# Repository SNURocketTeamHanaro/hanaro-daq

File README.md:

# Hanaro DAQ
A simple, low-cost, crude data acquisition system for combustion test of solid rocket motor.

### Specification
Hanaro DAQ for 200kgf horizontal combustion test system is a super low-cost data acquisition system. Equipped with two transducer for pressure sensor on the left and right side of the chamber top, and an instrumental amplifier for a single 200kgf load cell. Data is retrieved and recorded every 6-7 ms.

### Contents
- Hanaro DAQ PCB board designed with KiCAD v5.0.0
- Simple Arduino code for acquisition of data
- Data acquired with the system

### Credit
[Jaerin Lee](https://github.com/ironjr)  
Lead Electronics and Software Developer  
SNU Rocket Team Hanaro

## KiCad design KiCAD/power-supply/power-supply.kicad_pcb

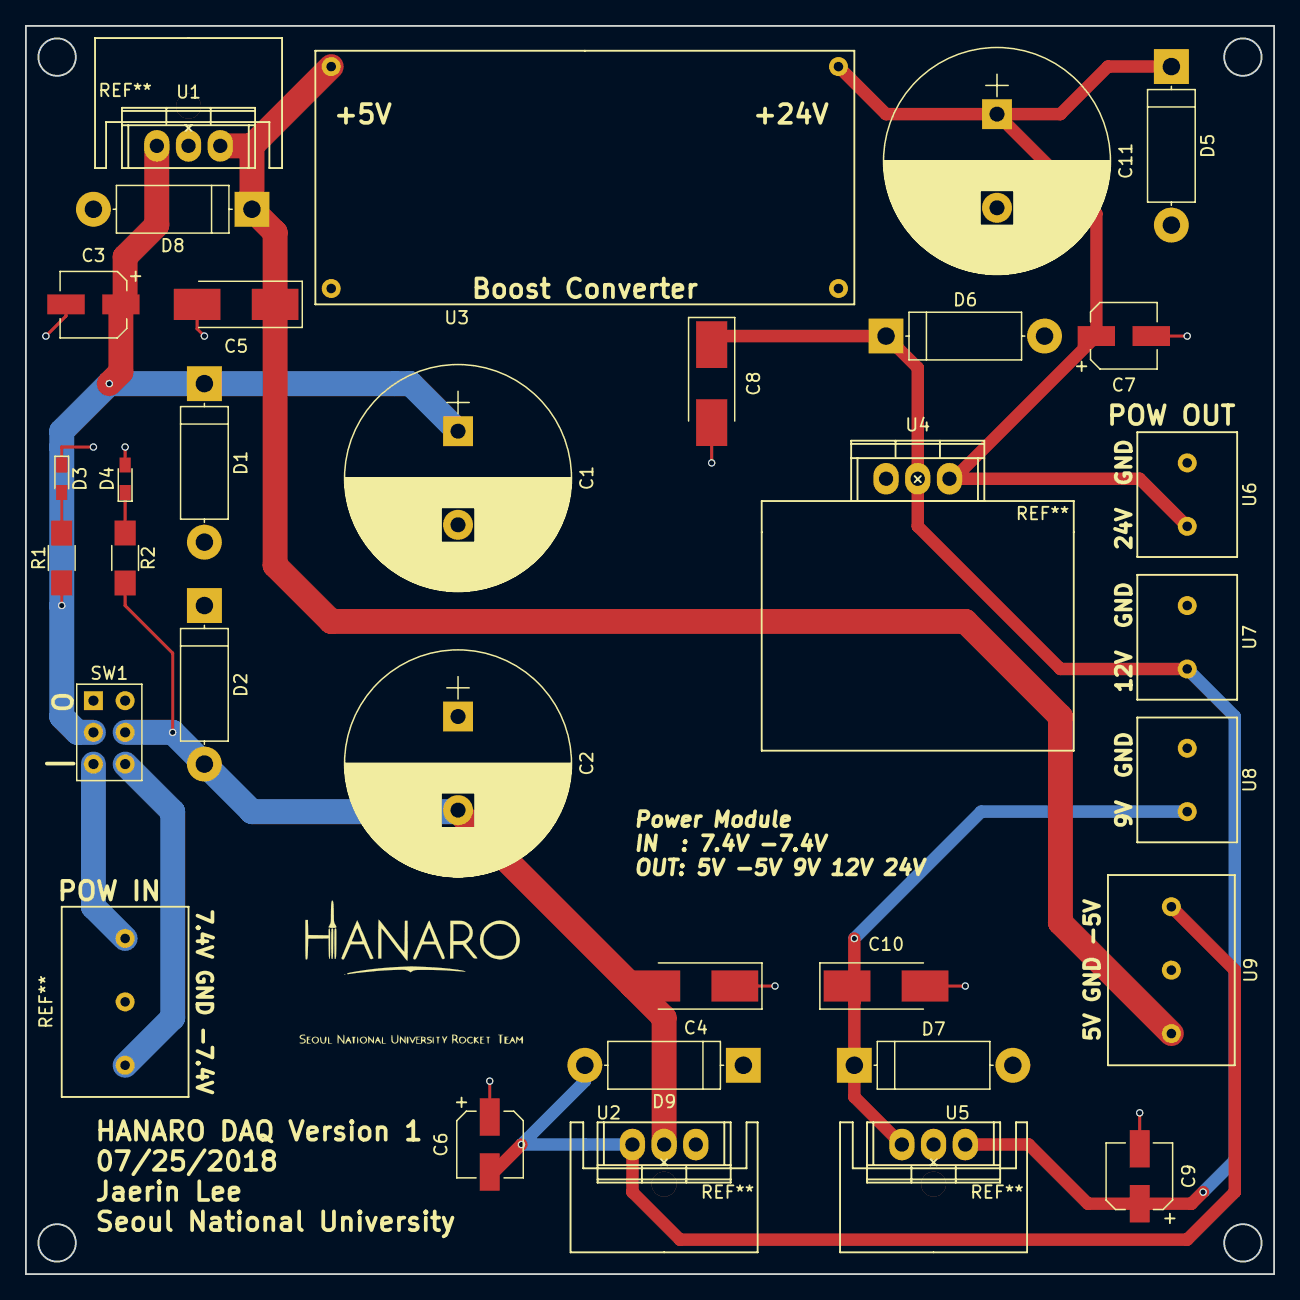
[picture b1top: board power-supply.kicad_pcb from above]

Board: 2 copper layers, 100.0 x 100.0 mm, 32 parts (0 on the bottom side), 10 nets.

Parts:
C1, C2, C11: CP1; CP_Radial_D18.0mm_P7.50mm
C3, C6, C7, C9: CP1; CP_Elec_5x5.3
C4, C5, C8, C10: CP1; CP_Tantalum_Case-C_EIA-6032-28_Hand
D1, D2, D5, D6, D7, D8, D9: D; D_5W_P12.70mm_Horizontal
D3, D4: LED; LED_0603_HandSoldering
R1, R2: R; R_1206_HandSoldering
SW1: SW_DPDT_x2; SW_NKK_G1xJP
U1: L7805; TO-220
U2: L7905; TO-220
U3: BoostConv; Boost.Conv
U4: LM1085-12; TO-220
U5: L7809; TO-220
U6, U7, U8: Conn2; Connector.2pin
U9: Conn3; Connector.3pin

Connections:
/V5out: C5.1, D8.1, U1.3, U3.1, U9.1
/V9out: C10.1, D7.1, U5.3, U8.1
/V12out: C8.1, C9.1, D6.1, U4.2, U5.1, U7.1
/V24out: C7.1, C11.1, D5.1, U3.3, U4.3, U6.1
/V-5out: C6.2, D9.2, U2.3, U9.3
GND: C1.2, C2.1, C3.2, C4.1, C5.2, C6.1, C7.2, C8.2, C9.2, C10.2, C11.2, D1.2, D2.1, D3.1, D4.2, D5.2, D6.2, D7.2, D8.2, D9.1, U1.2, U2.1, U3.2, U3.4, U4.1, U5.2, U6.2, U7.2, U8.2, U9.2
unnamed: C1.1, C3.1, D1.1, R1.1, SW1.2, U1.1
unnamed: C2.2, C4.2, D2.2, R2.2, SW1.5, U2.2
unnamed: D3.2, R1.2
unnamed: D4.1, R2.1

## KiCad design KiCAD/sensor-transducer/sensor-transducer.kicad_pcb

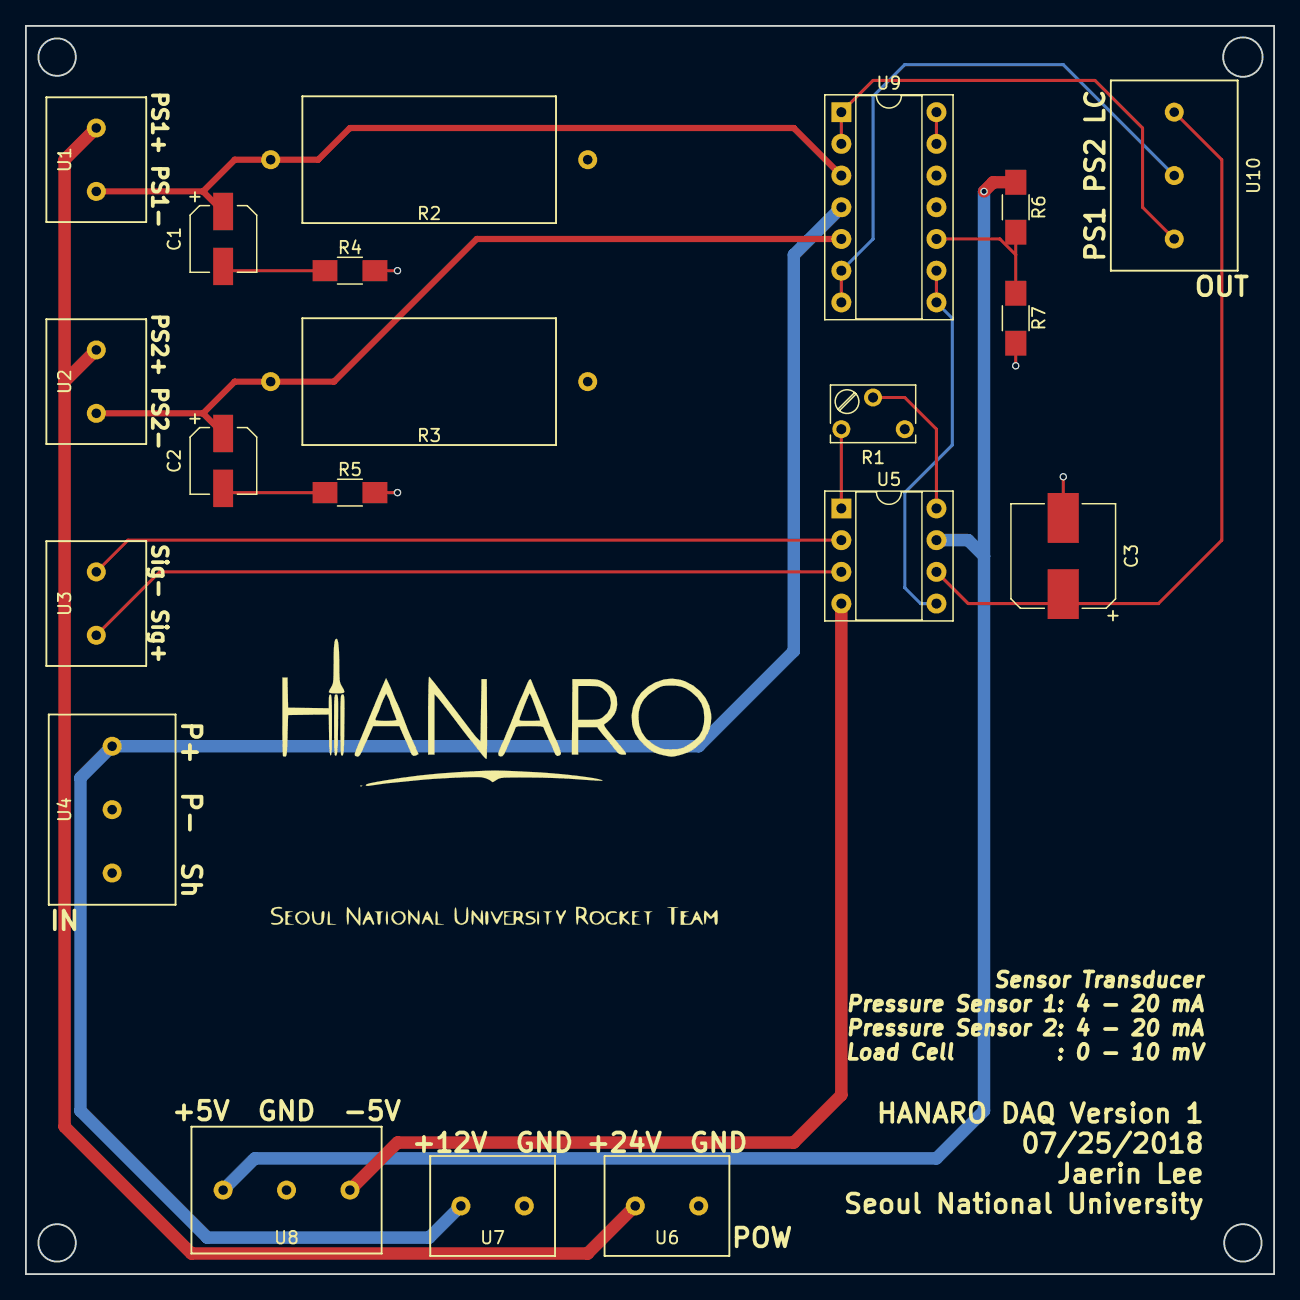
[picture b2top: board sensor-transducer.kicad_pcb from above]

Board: 2 copper layers, 100.0 x 100.0 mm, 20 parts (0 on the bottom side), 19 nets.

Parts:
C1, C2: CP1; CP_Elec_5x5.3
C3: CP1; CP_Elec_8x10
R1: R_Variable; Potentiometer_Trimmer_Bourns_3266W
R2, R3: R; Register.Cement.Square.Large
R4, R5, R6, R7: R; R_1206_HandSoldering
U1, U2, U3, U6, U7: Conn2; Connector.2pin
U4, U8, U10: Conn3; Connector.3pin
U5: AD620; DIP-8_W7.62mm_Socket
U9: LM324; DIP-14_W7.62mm_Socket

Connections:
+5V: R6.1, U5.7, U8.1
+12V: U4.1, U7.1, U9.4
-9VA: U5.4, U8.3
/24V+: U1.1, U2.1, U6.1
/AD620Ref: U5.5, U9.8, U9.9
/LCSig+: U3.2, U5.3
/LCSig-: U3.1, U5.2
/LCout: C3.1, U5.6, U10.3
/PS1-: C1.1, R2.1, U1.2, U9.3
/PS1out: U9.1, U9.2, U10.1
/PS2-: C2.1, R3.1, U2.2, U9.5
/PS2out: U9.6, U9.7, U10.2
GND: C3.2, R2.2, R3.2, R4.2, R5.2, R7.2, U4.2, U4.3, U6.2, U7.2, U8.2, U9.11
unnamed: C1.2, R4.1
unnamed: C2.2, R5.1
unnamed: R1.1, U5.1
unnamed: R1.2, U5.8
unnamed: R6.2, R7.1, U9.10
unnamed: U9.13, U9.14

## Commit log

2018-10-29 Current progress on data processing.
2018-10-29 added KiCAD PCB designs
2019-01-12 added old legacy
